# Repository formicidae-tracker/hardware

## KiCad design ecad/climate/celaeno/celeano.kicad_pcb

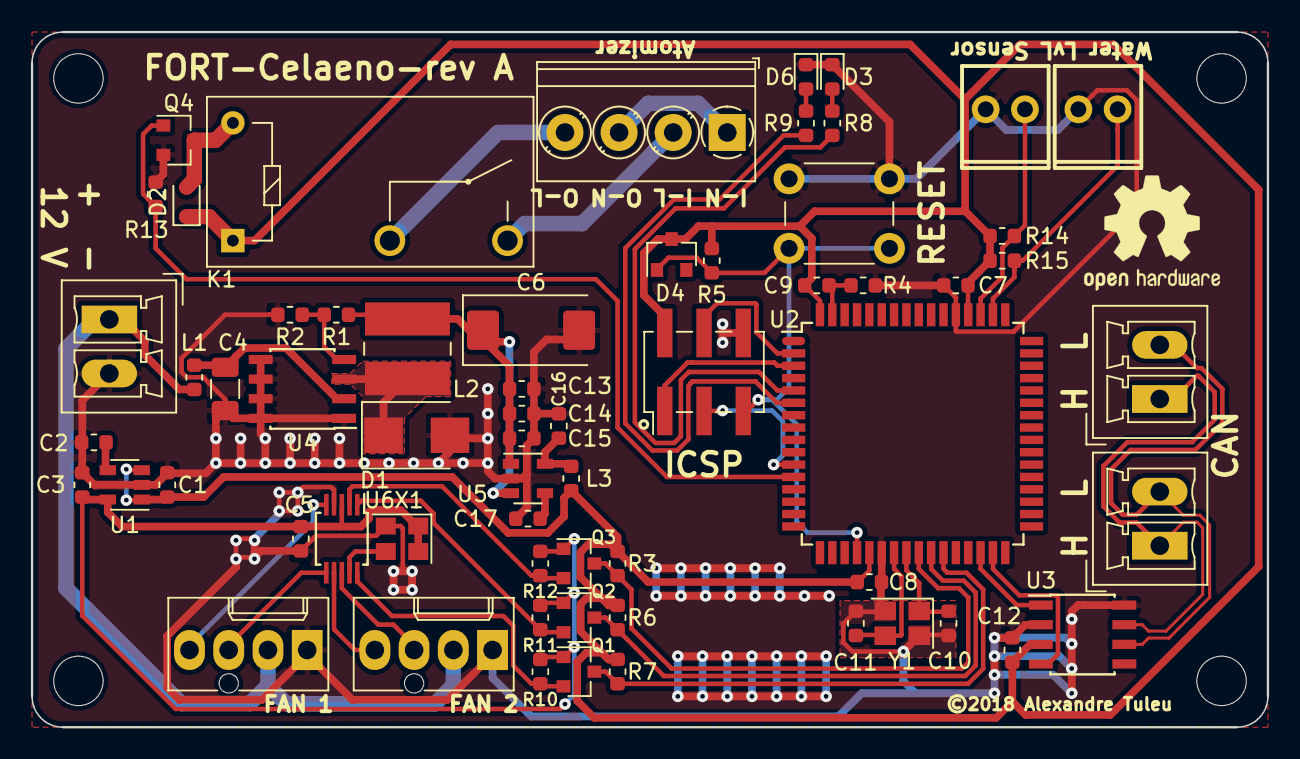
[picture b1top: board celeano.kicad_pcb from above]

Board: 2 copper layers, 80.0 x 45.0 mm, 63 parts (0 on the bottom side), 44 nets.

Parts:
C1, C3: 1uF; C_0603_1608Metric
C2: 10nF; C_0603_1608Metric
C4: 22uF, 35V; C_1206_3216Metric
C5: 100nF; C_0603_1608Metric
C6: 470u, 6.3V; CP_EIA-7343-31_Kemet-D
C7, C8, C9, C12, C14: 100n; C_0603_1608Metric
C10, C11: 18pF; C_0603_1608Metric
C13: 4u7, 6.3V; C_0603_1608Metric
C15, C16: 1u; C_0603_1608Metric
C17: 10n; C_0603_1608Metric
D1: B260, 60V, 2A; D_SMB
D2: 1N4148WS; D_SOD-323F
D3: GREEN; LED_0603_1608Metric
D4: BAT54; D_SOT-23_ANK
D6: YELLOW; LED_0603_1608Metric
J1, J2, J3: MCV 1,5/ 2-G-3,5; PhoenixContact_MCV_1,5_2-G-3.5_1x02_P3.50mm_Vertical
J4: M20-8760342; PinHeader_2x03_P2.54mm_Vertical_SMD
J5, J6: 47053-1000; Molex_KK-47053-04_04x2.54mm_Straight
J7: PT 1,5/4-3,5-H; TerminalBlock_Phoenix_PT-1,5-4-3.5-H_1x04_P3.50mm_Horizontal
J8, J9: 640454-2
K1: G5Q-1A4-EU DC5; Relay_SPST_Omron-G5Q-1A
L1, L3: 500mA Fuse; R_0603_1608Metric
L2: 68uH, 560mA; L_Wuerth_WE-PD2-Typ-MS
Q1, Q2, Q3, Q4: BSS138; SOT-23
R1: 15k; R_0603_1608Metric
R2: 4k32; R_0603_1608Metric
R3, R6, R7, R10, R11, R12: 10k; R_0603_1608Metric
R4: 0R; R_0603_1608Metric
R5, R14, R15: 100k; R_0603_1608Metric
R8, R9: 1k; R_0603_1608Metric
R13: 47k5; R_0603_1608Metric
SW1: 1825910-6; SW_PUSH_6mm
U1: LP3985IM5-3.3/NOPB; SOT-23-5
U2: AT90CAN128-16AU; TQFP-64_14x14mm_P0.8mm
U3: MCP2561-E/SN; SOIC-8_3.9x4.9mm_P1.27mm
U4: MIC4680YM; SOIC-8_3.9x4.9mm_P1.27mm
U5: LP3985IM5-5.0_NOPB; SOT-23-5
U6: EMC2302-1-AIZL-TR; MSOP-10_3x3mm_P0.5mm
X1: 32.768kHz; Oscillator_SMD_Abracon_ASE-4Pin_3.2x2.5mm
Y1: 16MHz; Crystal_SMD_SeikoEpson_FA238-4Pin_3.2x2.5mm

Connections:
+3V3: C3.1, C5.1, Q1.1, Q2.1, Q3.1, R10.1, R11.1, R12.1, U1.5, U6.3, X1.1, X1.4
+5V: C1.1, C7.1, C8.1, C9.1, C12.1, D2.1, D4.1, J4.2, K1.1, L3.1, R3.1, R5.1, R6.1, R7.1, R14.1, R15.1, U1.1, U1.3, U2.21, U2.52, U2.64, U3.3
+12V: J3.1, J5.2, J6.2, L1.2
/3v3 LDO/BYPASS: C2.1, U1.4
/5V Buck Converter/5V5_UNPROTECTED: C6.1, C13.1, C14.1, C15.1, L2.2, R1.1, U5.1, U5.3
/5V Buck Converter/5V_UNPROTECTED: C16.1, L3.2, U5.5
/5V Buck Converter/FB: R1.2, R2.1, U4.4
/5V Buck Converter/SW: D1.1, L2.1, U4.3
/5V Buck Converter/VIN_PROTECTED: C4.1, L1.1, U4.2
/CAN Transceiver/CAN+: J1.1, J2.1, U3.7
/CAN Transceiver/CAN-: J1.2, J2.2, U3.6
/Fan PWM Controller 1/32K768_CLK: U6.9, X1.3
/Fan PWM Controller 1/PWM1: J5.4, U6.5
/Fan PWM Controller 1/PWM2: J6.4, U6.7
/Fan PWM Controller 1/SCL: Q3.2, R12.2, U6.2
/Fan PWM Controller 1/SDA: Q2.2, R11.2, U6.1
/Fan PWM Controller 1/TACH1: J5.3, U6.6
/Fan PWM Controller 1/TACH2: J6.3, U6.8
/Fan PWM Controller 1/~ALERT: Q1.2, R10.2, U6.10
/I2C Level Shifter/SCL_5V: Q3.3, R3.2, U2.25
/I2C Level Shifter/SDA_5V: Q2.3, R6.2, U2.26
/Relay/A: J7.2, K1.3
/Relay/B: J7.4, K1.2
/Relay/CMD: Q4.1, R13.2, U2.12
/UC/CAN_RX: U2.31, U3.4
/UC/CAN_TX: U2.30, U3.1
/UC/ICSP_MISO: J4.1, U2.3
/UC/ICSP_MOSI: J4.4, U2.2
/UC/ICSP_SCK: J4.3, U2.11
/UC/LED_GREEN: R8.1, U2.5
/UC/LED_YELLOW: R9.1, U2.6
/UC/LVL_0: J8.1, R14.2, U2.51
/UC/LVL_1: J9.1, R15.2, U2.50
/UC/XTAL+: C10.2, U2.24, Y1.1
/UC/XTAL-: C11.2, U2.23, Y1.3
/UC/~FAN_ALERT: Q1.3, R7.2, U2.27
/UC/~ICSP_RESET: D4.2, J4.5, R5.2, SW1.2, U2.20
GND: C1.2, C2.2, C3.2, C4.2, C5.2, C6.2, C7.2, C8.2, C10.1, C11.1, C12.2, C13.2, C14.2, C15.2, C16.2, C17.2, D1.2, D3.1, D6.1, J3.2, J4.6, J5.1, J6.1, J8.2, J9.2, Q4.2, R2.2, R4.2, R13.1, SW1.1, U1.2, U2.22, U2.53, U3.2, U3.8, U4.1, U4.5, U4.6, U4.7, U4.8, U5.2, U6.4, X1.2, Y1.2, Y1.4
GNDA: C9.2, R4.1, U2.63
unnamed: C17.1, U5.4
unnamed: D2.2, K1.5, Q4.3
unnamed: D3.2, R8.2
unnamed: D6.2, R9.2
unnamed: J7.1, J7.3

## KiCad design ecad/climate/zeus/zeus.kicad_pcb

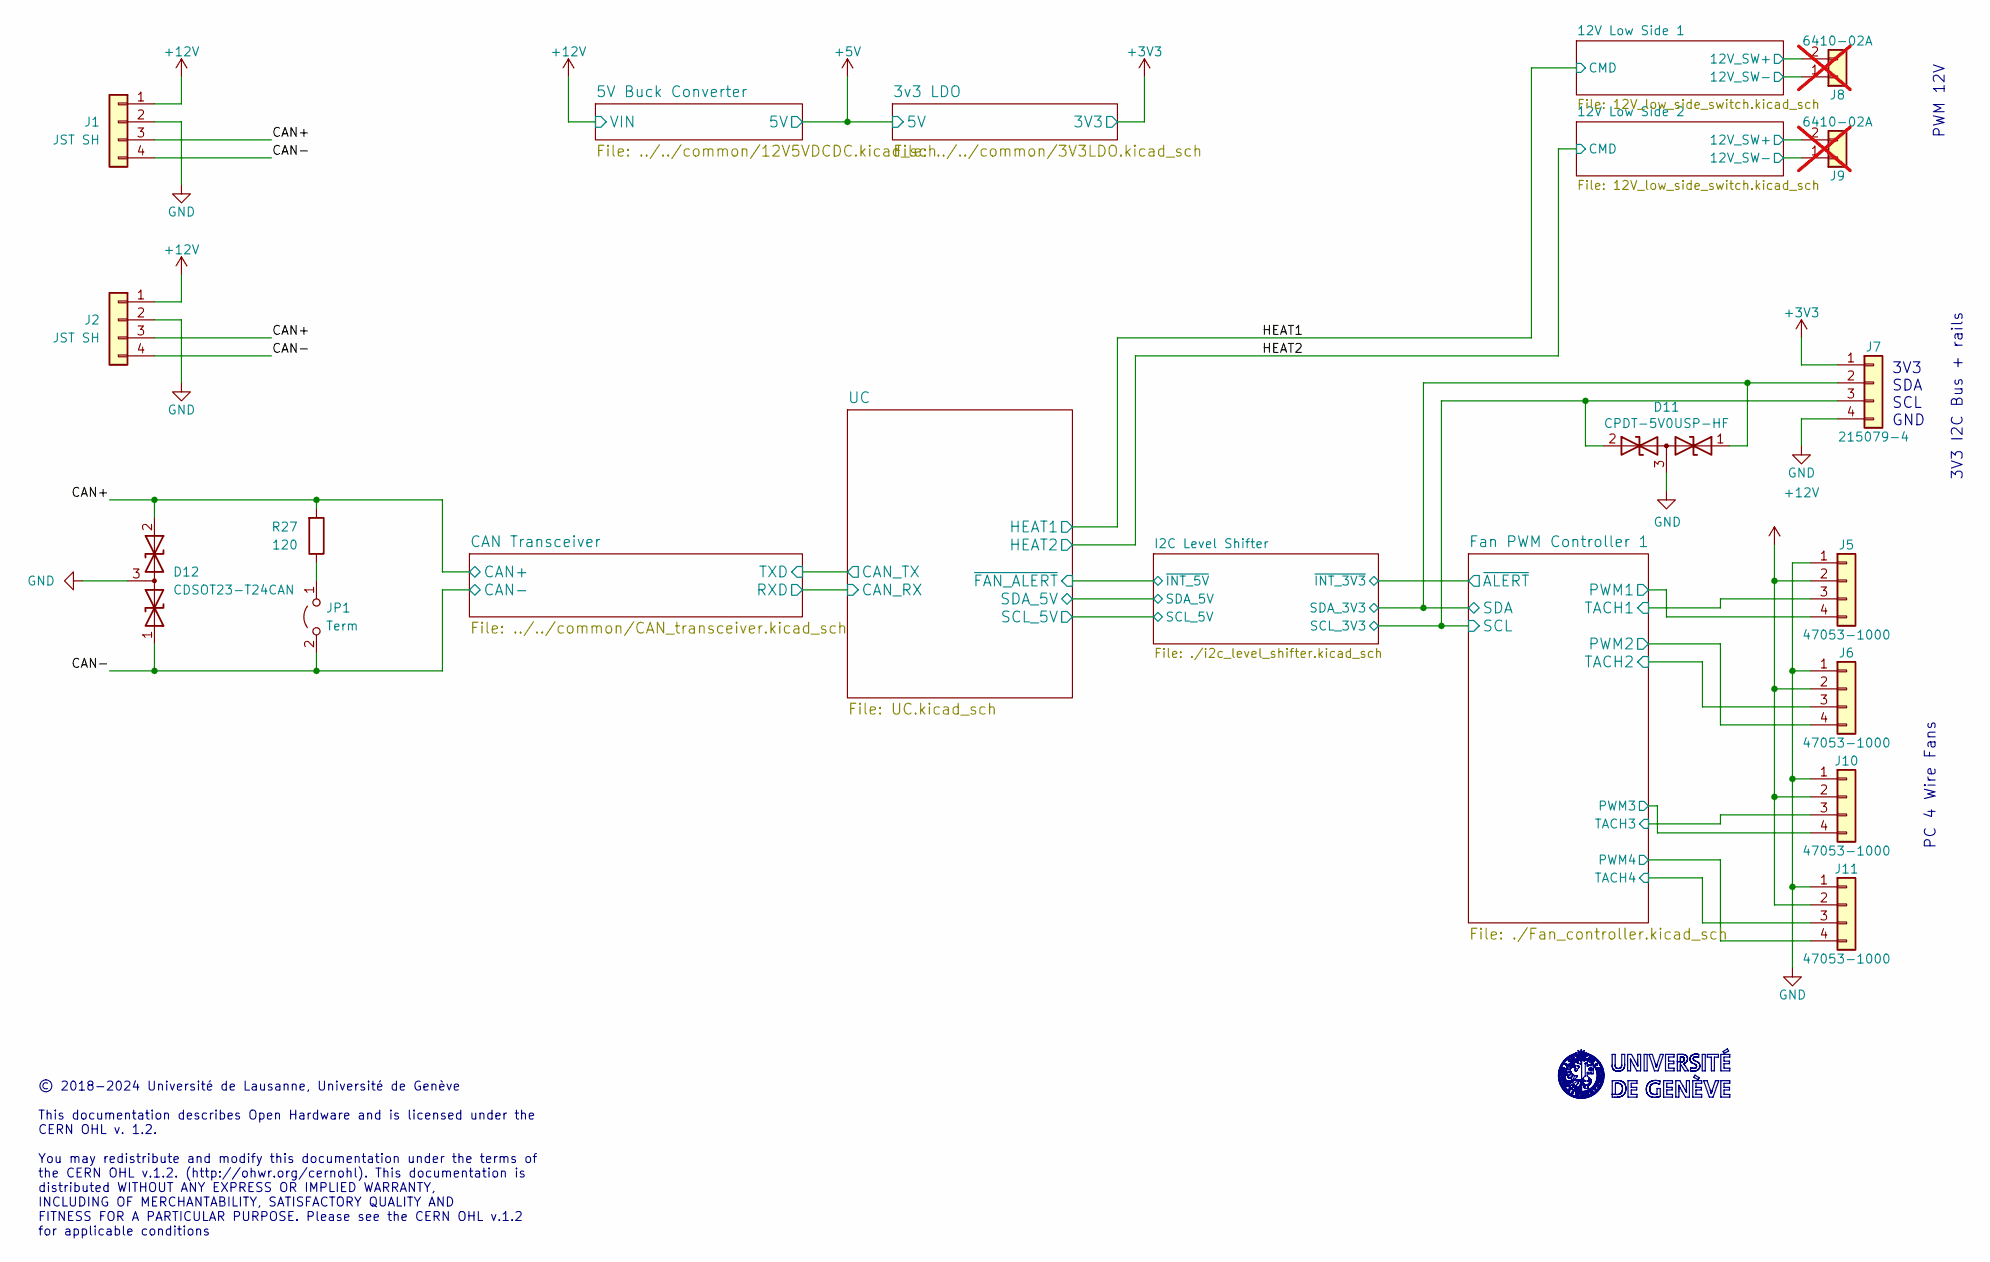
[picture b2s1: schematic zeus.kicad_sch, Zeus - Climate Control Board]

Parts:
D11: CPDT-5V0USP-HF; SOT-23; MPN CPDT-5V0USP-HF
D12: CDSOT23-T24CAN; SOT-23; MPN CDSOT23-T24CAN
J1, J2: JST SH; JST_PH_B4B-PH-SM4-TB_1x04-1MP_P2.00mm_Vertical; MPN B4B-PH-SM4
J5, J6, J10, J11: 47053-1000; Molex_KK-47053-04_04x2.54mm_Straight; MPN 47053-1000
J7: 215079-4; Micro-Match_4_TH; MPN 215079-4
J8, J9: 6410-02A; Molex_KK-254_AE-6410-02A_1x02_P2.54mm_Vertical; MPN 6410-02A; not fitted
JP1: Term; PinHeader_1x02_P2.54mm_Vertical; MPN GPHA-1X02
R27: 120; R_0603_1608Metric; MPN GPR0603120R

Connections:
+3V3: J7.1; also elsewhere on the board
+12V: J1.1, J2.1, J5.2, J6.2, J8.2, J9.2, J10.2, J11.2; also elsewhere on the board
/12V Low Side 1/SW_RTRN: J8.1; also elsewhere on the board
/12V Low Side 2/SW_RTRN: J9.1; also elsewhere on the board
/CAN+: D12.2 (A2), J1.3, J2.3, R27.2; also elsewhere on the board
/CAN-: D12.1 (A1), J1.4, J2.4, JP1.2 (B); also elsewhere on the board
/Fan PWM Controller 1/PWM1: J5.4; also elsewhere on the board
/Fan PWM Controller 1/PWM2: J6.4; also elsewhere on the board
/Fan PWM Controller 1/PWM3: J10.4; also elsewhere on the board
/Fan PWM Controller 1/PWM4: J11.4; also elsewhere on the board
/Fan PWM Controller 1/SCL: D11.2 (A2), J7.3; also elsewhere on the board
/Fan PWM Controller 1/SDA: D11.1 (A1), J7.2; also elsewhere on the board
/Fan PWM Controller 1/TACH1: J5.3; also elsewhere on the board
/Fan PWM Controller 1/TACH2: J6.3; also elsewhere on the board
/Fan PWM Controller 1/TACH3: J10.3; also elsewhere on the board
/Fan PWM Controller 1/TACH4: J11.3; also elsewhere on the board
GND: D11.3 (common), D12.3 (common), J1.2, J2.2, J5.1, J6.1, J7.4, J10.1, J11.1; also elsewhere on the board
unnamed: JP1.1 (A), R27.1

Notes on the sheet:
3V3 I2C Bus + rails
© 2018-2024 Université de Lausanne, Université de Genève This documentation describes Open Hardware and is licensed under the CERN OHL v. 1.2. You may redistribute and modify this documentation under the terms of the CERN OHL v.1.2. (http://ohwr.org/cernohl). This documentation is distributed WITHO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
3V3 SDA SCL GND
PWM 12V
PC 4 Wire Fans

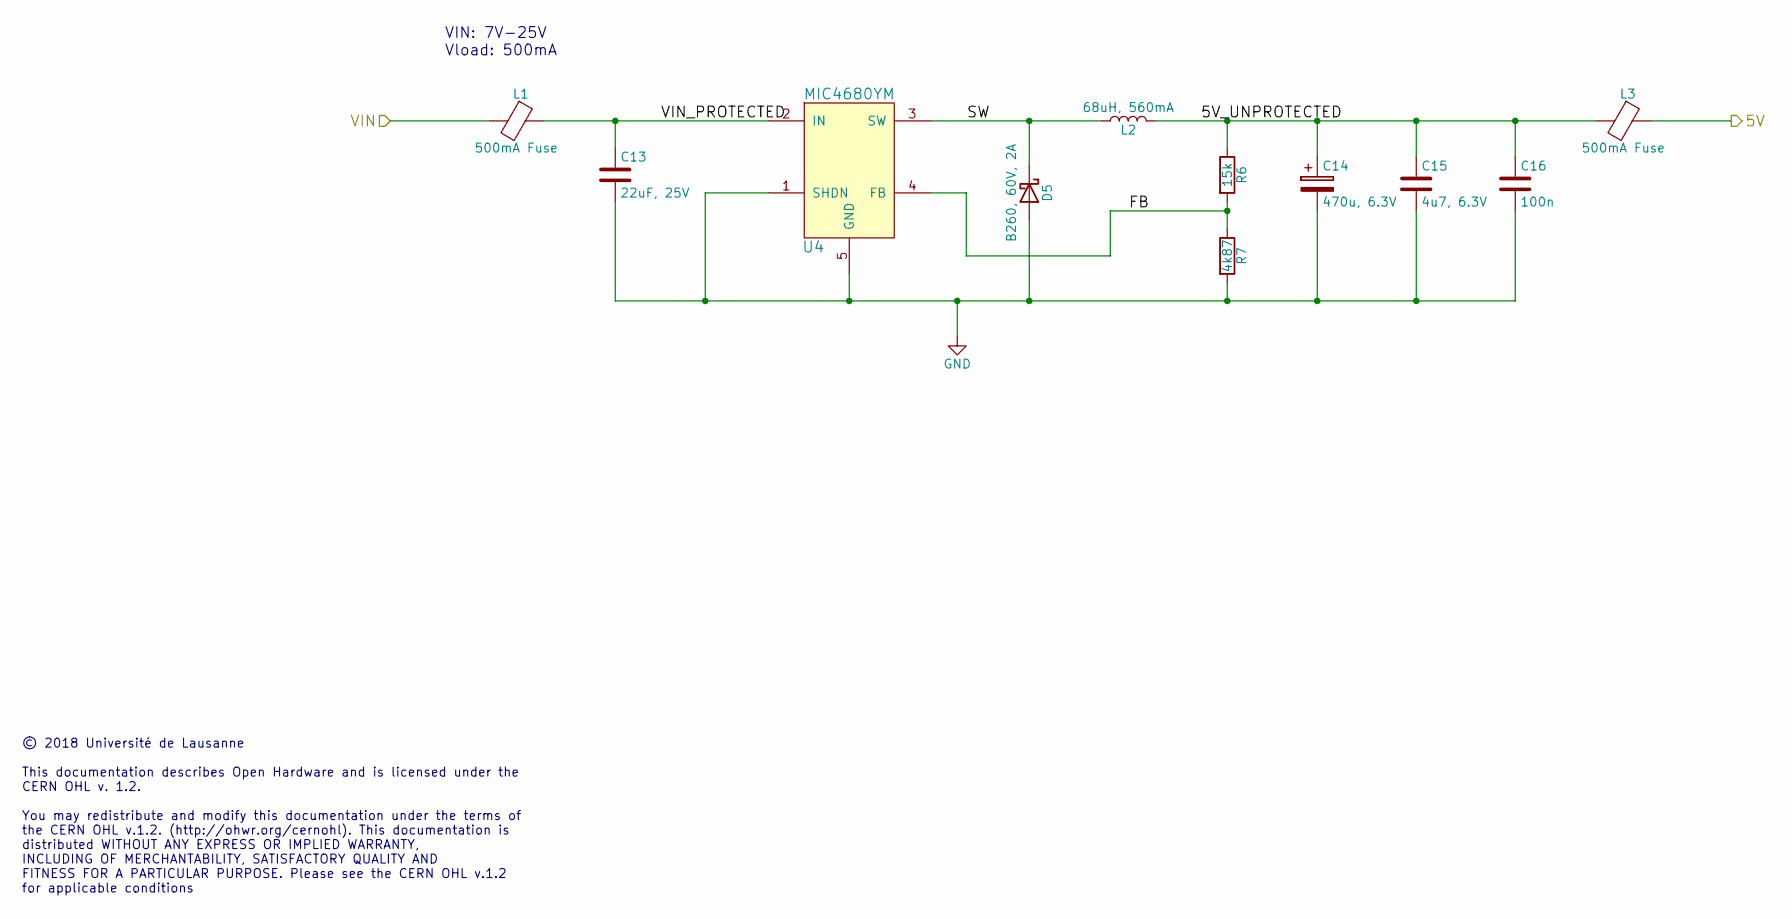
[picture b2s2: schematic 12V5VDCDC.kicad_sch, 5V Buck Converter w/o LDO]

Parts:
C13: 22uF, 25V; C_1206_3216Metric; MPN CL31A226KAHNNNE
C14: 470u, 6.3V; CP_EIA-7343-31_Kemet-D
C15: 4u7, 6.3V; C_0603_1608Metric
C16: 100n; C_0603_1608Metric; MPN GPC0603104
D5: B260, 60V, 2A; D_SMB
L1, L3: 500mA Fuse; R_0603_1608Metric
L2: 68uH, 560mA; L_Wuerth_WE-PD2-Typ-MS
R6: 15k; R_0603_1608Metric
R7: 4k87; R_0603_1608Metric
U4: MIC4680YM; SOIC-8_3.9x4.9mm_P1.27mm

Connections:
+5V: L3.1; also elsewhere on the board
+12V: L1.2; also elsewhere on the board
/5V Buck Converter/5V_UNPROTECTED: C14.1, C15.1, C16.1, L2.2, L3.2, R6.1
/5V Buck Converter/FB: R6.2, R7.1, U4.4 (FB)
/5V Buck Converter/SW: D5.1 (K), L2.1, U4.3 (SW)
/5V Buck Converter/VIN_PROTECTED: C13.1, L1.1, U4.2 (IN)
GND: C13.2, C14.2, C15.2, C16.2, D5.2 (A), R7.2, U4.1 (SHDN), U4.5 (GND), U4.6 (GND), U4.7 (GND), U4.8 (GND); also elsewhere on the board

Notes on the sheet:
© 2018 Université de Lausanne This documentation describes Open Hardware and is licensed under the CERN OHL v. 1.2. You may redistribute and modify this documentation under the terms of the CERN OHL v.1.2. (http://ohwr.org/cernohl). This documentation is distributed WITHOUT ANY EXPRESS OR IMPLIED W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
VIN: 7V-25V Vload: 500mA

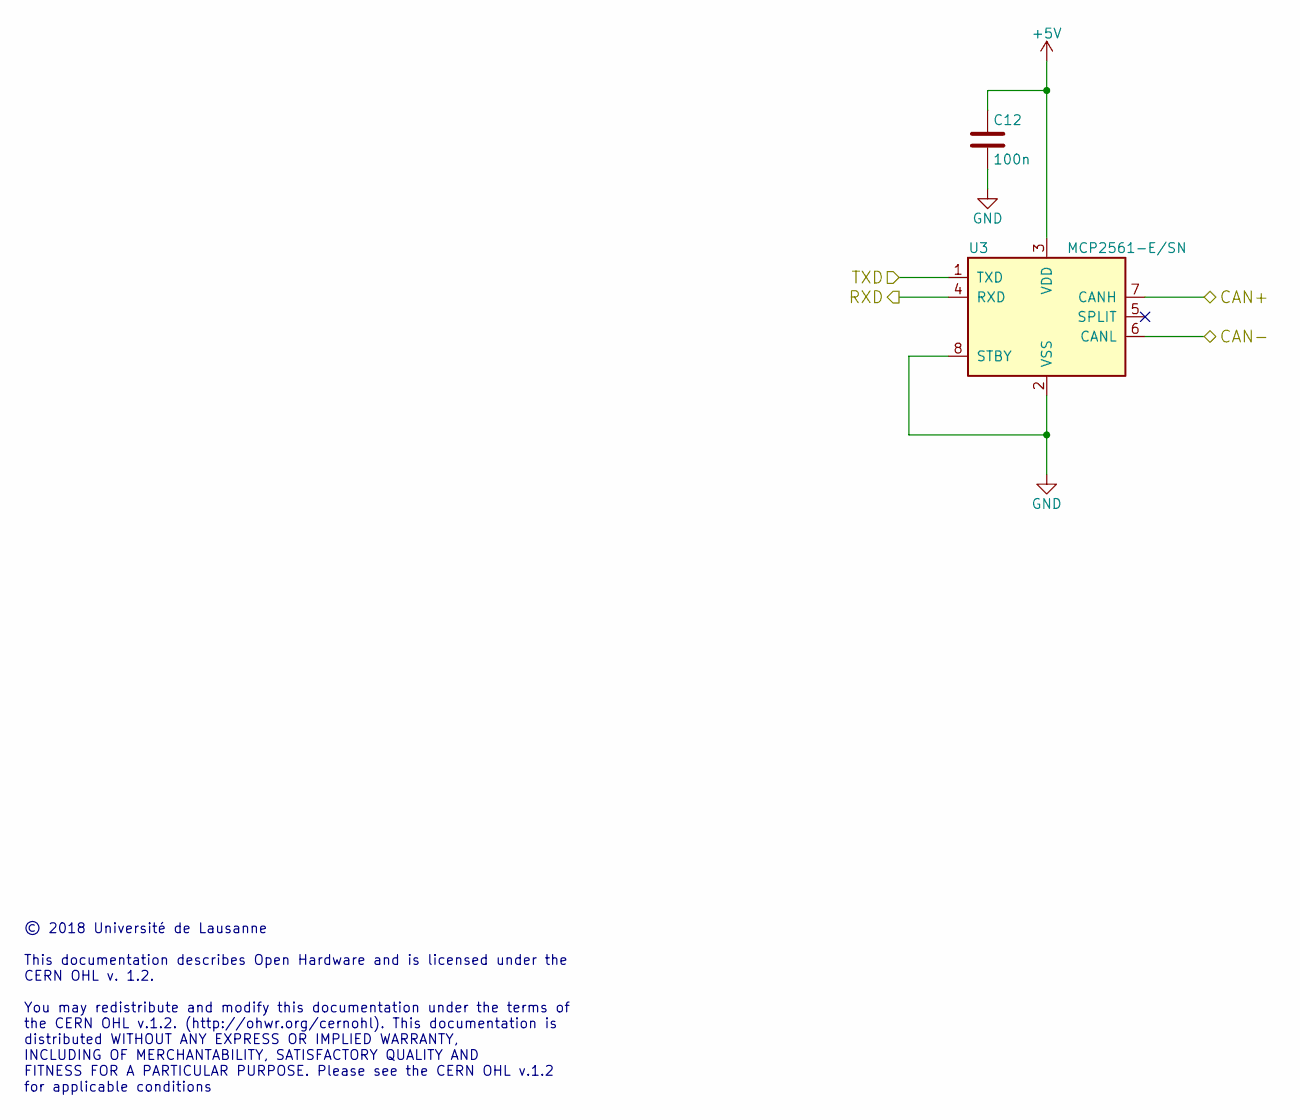
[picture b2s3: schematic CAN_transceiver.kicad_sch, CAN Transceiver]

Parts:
C12: 100n; C_0603_1608Metric; MPN GPC0603104
U3: MCP2561-E/SN; SOIC-8_3.9x4.9mm_P1.27mm

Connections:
+5V: C12.1, U3.3 (VDD); also elsewhere on the board
/CAN Transceiver/RXD: U3.4 (RXD); also elsewhere on the board
/CAN Transceiver/TXD: U3.1 (TXD); also elsewhere on the board
/CAN+: U3.7 (CANH); also elsewhere on the board
/CAN-: U3.6 (CANL); also elsewhere on the board
GND: C12.2, U3.2 (VSS), U3.8 (STBY); also elsewhere on the board

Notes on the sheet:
© 2018 Université de Lausanne This documentation describes Open Hardware and is licensed under the CERN OHL v. 1.2. You may redistribute and modify this documentation under the terms of the CERN OHL v.1.2. (http://ohwr.org/cernohl). This documentation is distributed WITHOUT ANY EXPRESS OR IMPLIED W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

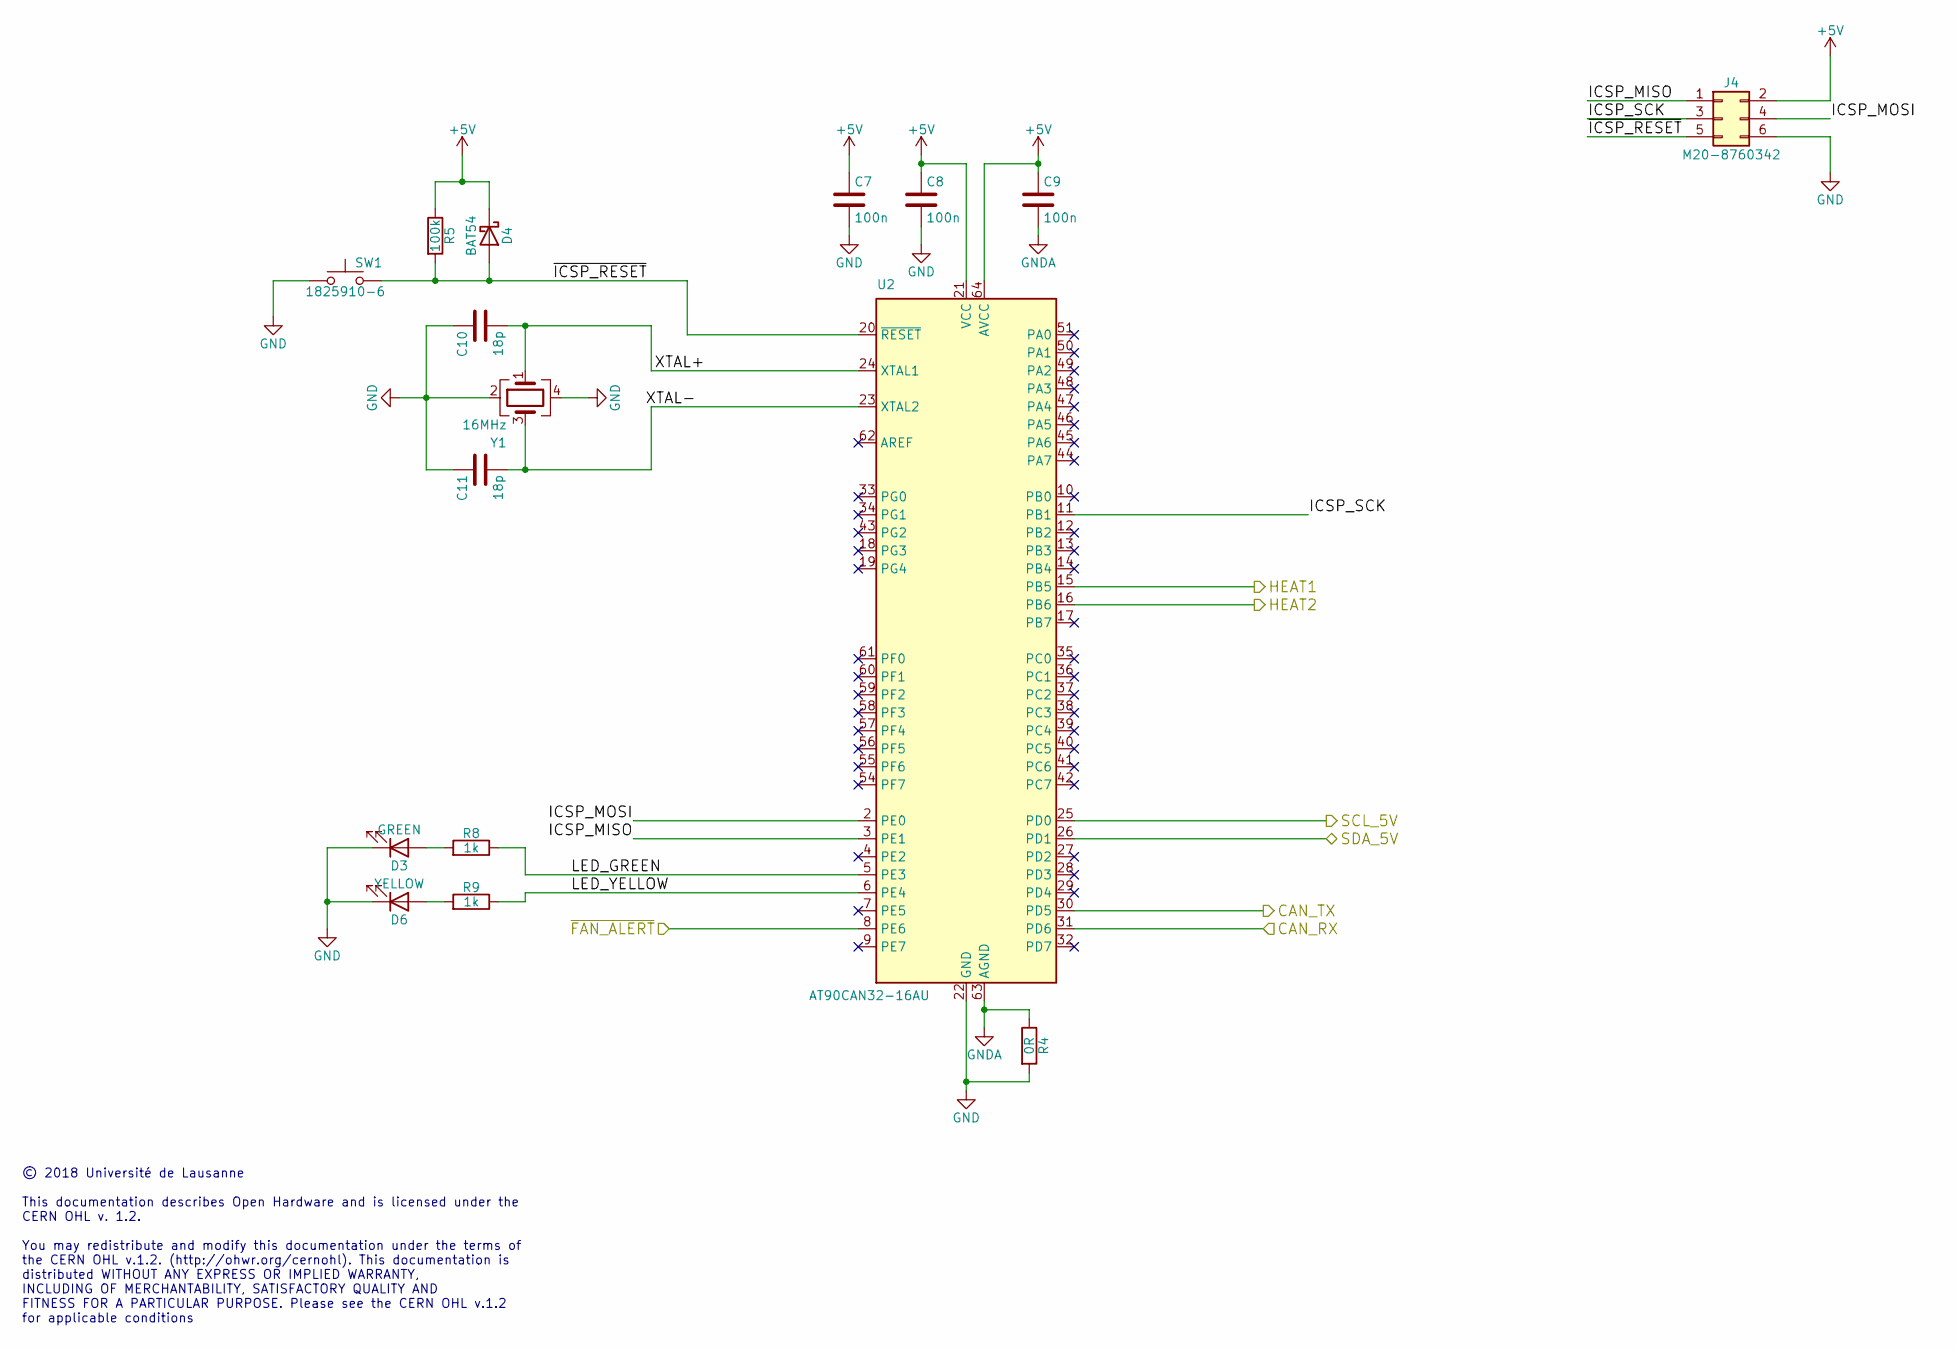
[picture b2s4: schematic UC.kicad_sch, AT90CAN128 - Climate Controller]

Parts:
C7, C8, C9: 100n; C_0603_1608Metric; MPN GPC0603104
C10, C11: 18p; C_0603_1608Metric; MPN GPC0603180
D3: GREEN; LED_0603_1608Metric; MPN 150060VS75000
D4: BAT54; D_SOT-23_ANK; MPN BAT54-7-F
D6: YELLOW; LED_0603_1608Metric; MPN 150060YS75000
J4: M20-8760342; PinHeader_2x03_P2.54mm_Vertical_SMD; MPN M20-8760342
R4: 0R; R_0603_1608Metric; MPN GPR06030R
R5: 100k; R_0603_1608Metric; MPN GPR0603100K
R8, R9: 1k; R_0603_1608Metric; MPN GPR06031K
SW1: 1825910-6; SW_PUSH_6mm; MPN 1825910-6
U2: AT90CAN32-16AU; TQFP-64_14x14mm_P0.8mm; MPN AT90CAN32-16AU
Y1: 16MHz; Crystal_SMD_SeikoEpson_FA238-4Pin_3.2x2.5mm; MPN FA-238 16.0000MB-C3

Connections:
+5V: C7.1, C8.1, C9.1, D4.1 (K), J4.2, R5.1, U2.21 (VCC), U2.52 (VCC), U2.64 (AVCC); also elsewhere on the board
/CAN Transceiver/RXD: U2.31 (PD6); also elsewhere on the board
/CAN Transceiver/TXD: U2.30 (PD5); also elsewhere on the board
/I2C Level Shifter/SCL_5V: U2.25 (PD0); also elsewhere on the board
/I2C Level Shifter/SDA_5V: U2.26 (PD1); also elsewhere on the board
/I2C Level Shifter/~INT_5V: U2.8 (PE6); also elsewhere on the board
/UC/ICSP_MISO: J4.1, U2.3 (PE1)
/UC/ICSP_MOSI: J4.4, U2.2 (PE0)
/UC/ICSP_SCK: J4.3, U2.11 (PB1)
/UC/LED_GREEN: R8.1, U2.5 (PE3)
/UC/LED_YELLOW: R9.1, U2.6 (PE4)
/UC/XTAL+: C10.2, U2.24 (XTAL1), Y1.1
/UC/XTAL-: C11.2, U2.23 (XTAL2), Y1.3
/UC/~ICSP_RESET: D4.2 (A), J4.5, R5.2, SW1.2, U2.20 (~RESET)
GND: C7.2, C8.2, C10.1, C11.1, D3.1 (K), D6.1 (K), J4.6, R4.2, SW1.1, U2.22 (GND), U2.53 (GND), Y1.2, Y1.4; also elsewhere on the board
GNDA: C9.2, R4.1, U2.63 (AGND)
unnamed: D3.2 (A), R8.2
unnamed: D6.2 (A), R9.2

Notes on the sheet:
© 2018 Université de Lausanne This documentation describes Open Hardware and is licensed under the CERN OHL v. 1.2. You may redistribute and modify this documentation under the terms of the CERN OHL v.1.2. (http://ohwr.org/cernohl). This documentation is distributed WITHOUT ANY EXPRESS OR IMPLIED W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

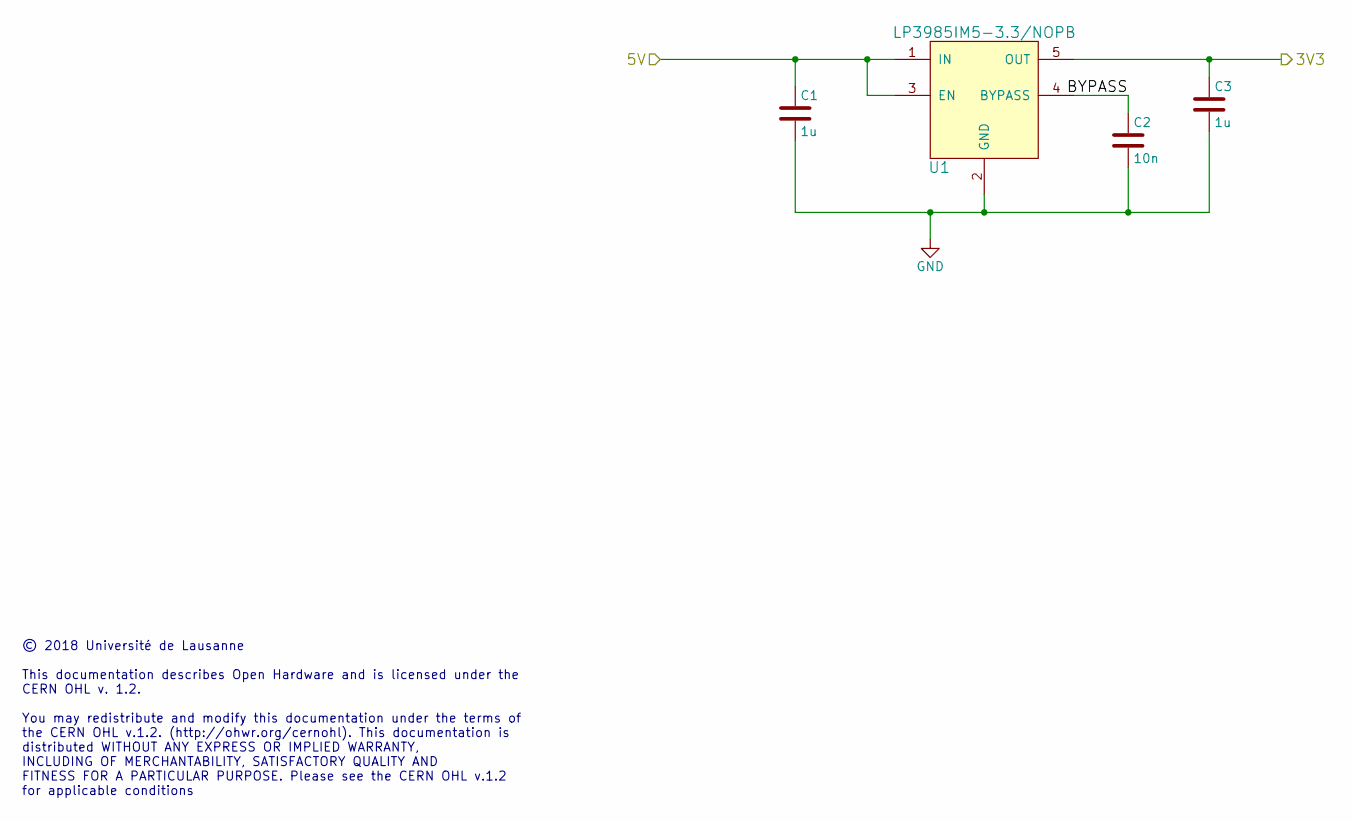
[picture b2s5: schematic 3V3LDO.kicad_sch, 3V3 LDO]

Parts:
C1, C3: 1u; C_0603_1608Metric; MPN GPC0603105
C2: 10n; C_0603_1608Metric; MPN GPC0603103
U1: LP3985IM5-3.3/NOPB; SOT-23-5

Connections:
+3V3: C3.1, U1.5 (OUT); also elsewhere on the board
+5V: C1.1, U1.1 (IN), U1.3 (EN); also elsewhere on the board
/3v3 LDO/BYPASS: C2.1, U1.4 (BYPASS)
GND: C1.2, C2.2, C3.2, U1.2 (GND); also elsewhere on the board

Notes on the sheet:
© 2018 Université de Lausanne This documentation describes Open Hardware and is licensed under the CERN OHL v. 1.2. You may redistribute and modify this documentation under the terms of the CERN OHL v.1.2. (http://ohwr.org/cernohl). This documentation is distributed WITHOUT ANY EXPRESS OR IMPLIED W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

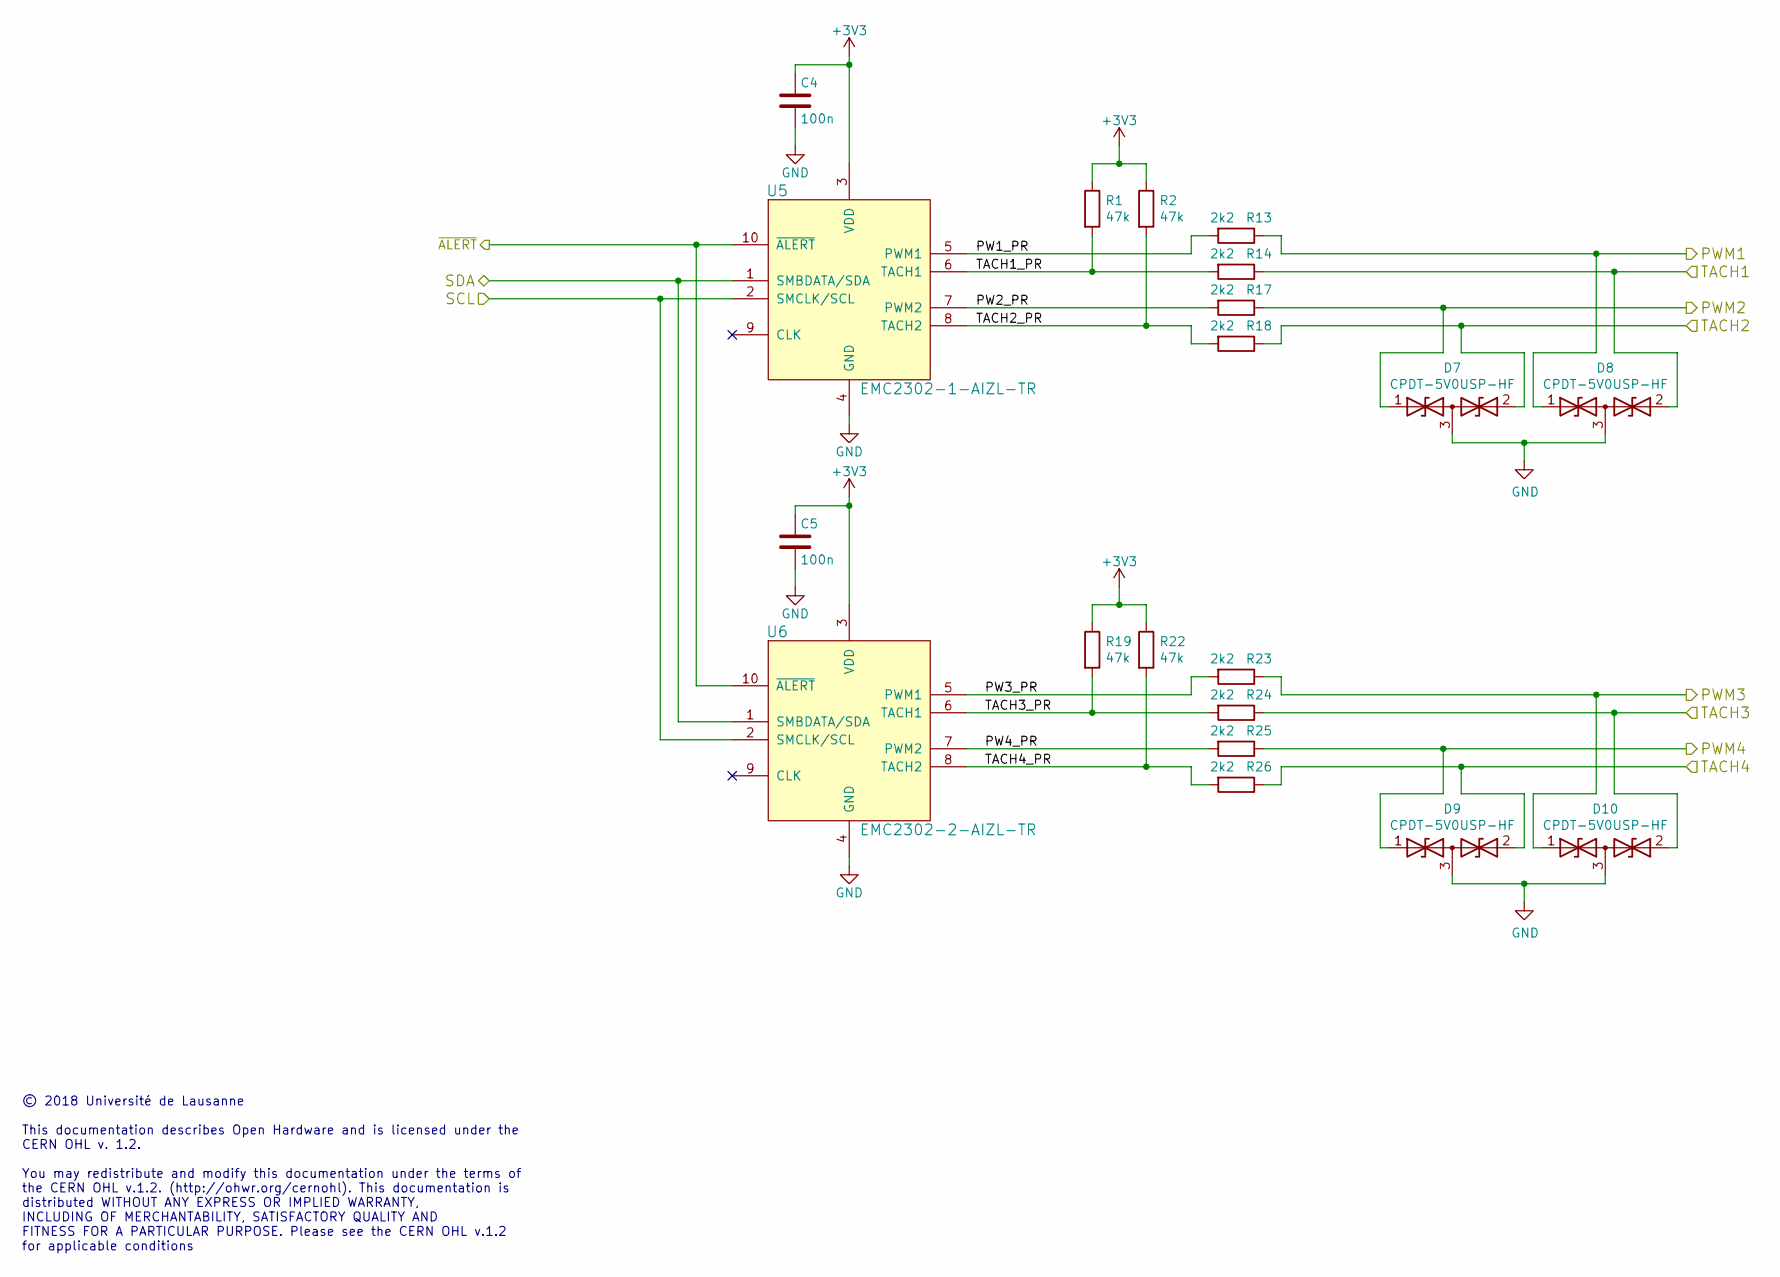
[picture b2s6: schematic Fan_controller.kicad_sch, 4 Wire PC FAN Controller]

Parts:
C4, C5: 100n; C_0603_1608Metric; MPN GPC0603104
D7, D8, D9, D10: CPDT-5V0USP-HF; SOT-23; MPN CPDT-5V0USP-HF
R1, R2, R19, R22: 47k; R_0603_1608Metric; MPN GPR060347K
R13, R14, R17, R18, R23, R24, R25, R26: 2k2; R_0603_1608Metric; MPN GPR06032K2
U5: EMC2302-1-AIZL-TR; MSOP-10_3x3mm_P0.5mm; MPN EMC2302-1-AIZL-TR
U6: EMC2302-2-AIZL-TR; MSOP-10_3x3mm_P0.5mm; MPN EMC2302-2-AIZL-TR

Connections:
+3V3: C4.1, C5.1, R1.1, R2.1, R19.1, R22.1, U5.3 (VDD), U6.3 (VDD); also elsewhere on the board
/Fan PWM Controller 1/PW1_PR: R13.2, U5.5 (PWM1)
/Fan PWM Controller 1/PW2_PR: R17.2, U5.7 (PWM2)
/Fan PWM Controller 1/PW3_PR: R23.2, U6.5 (PWM1)
/Fan PWM Controller 1/PW4_PR: R25.2, U6.7 (PWM2)
/Fan PWM Controller 1/PWM1: D8.1 (A1), R13.1; also elsewhere on the board
/Fan PWM Controller 1/PWM2: D7.1 (A1), R17.1; also elsewhere on the board
/Fan PWM Controller 1/PWM3: D10.1 (A1), R23.1; also elsewhere on the board
/Fan PWM Controller 1/PWM4: D9.1 (A1), R25.1; also elsewhere on the board
/Fan PWM Controller 1/SCL: U5.2 (SMCLK/SCL), U6.2 (SMCLK/SCL); also elsewhere on the board
/Fan PWM Controller 1/SDA: U5.1 (SMBDATA/SDA), U6.1 (SMBDATA/SDA); also elsewhere on the board
/Fan PWM Controller 1/TACH1: D8.2 (A2), R14.1; also elsewhere on the board
/Fan PWM Controller 1/TACH1_PR: R1.2, R14.2, U5.6 (TACH1)
/Fan PWM Controller 1/TACH2: D7.2 (A2), R18.1; also elsewhere on the board
/Fan PWM Controller 1/TACH2_PR: R2.2, R18.2, U5.8 (TACH2)
/Fan PWM Controller 1/TACH3: D10.2 (A2), R24.1; also elsewhere on the board
/Fan PWM Controller 1/TACH3_PR: R19.2, R24.2, U6.6 (TACH1)
/Fan PWM Controller 1/TACH4: D9.2 (A2), R26.1; also elsewhere on the board
/Fan PWM Controller 1/TACH4_PR: R22.2, R26.2, U6.8 (TACH2)
/Fan PWM Controller 1/~ALERT: U5.10 (~ALERT), U6.10 (~ALERT); also elsewhere on the board
GND: C4.2, C5.2, D7.3 (common), D8.3 (common), D9.3 (common), D10.3 (common), U5.4 (GND), U6.4 (GND); also elsewhere on the board

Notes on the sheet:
© 2018 Université de Lausanne This documentation describes Open Hardware and is licensed under the CERN OHL v. 1.2. You may redistribute and modify this documentation under the terms of the CERN OHL v.1.2. (http://ohwr.org/cernohl). This documentation is distributed WITHOUT ANY EXPRESS OR IMPLIED W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

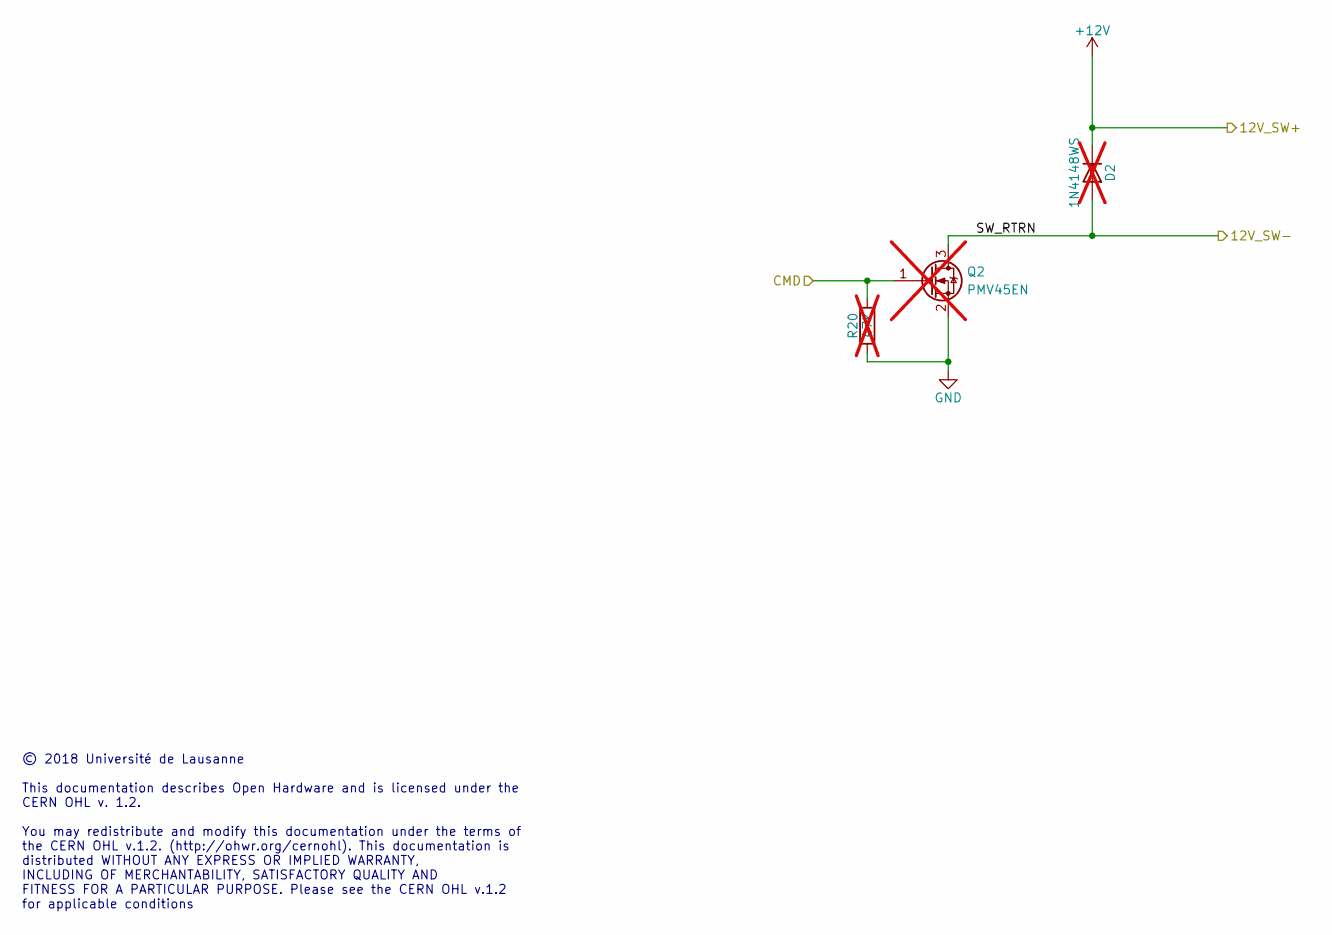
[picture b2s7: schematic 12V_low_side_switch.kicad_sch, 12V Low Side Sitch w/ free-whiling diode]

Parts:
D2: 1N4148WS; D_SOD-323F; MPN 1N4148WS; not fitted
Q2: PMV45EN; SOT-23; MPN PMV45EN2R; not fitted
R20: 47k; R_0603_1608Metric; MPN GPR060347K; not fitted

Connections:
+12V: D2.1 (K); also elsewhere on the board
/12V Low Side 2/SW_RTRN: D2.2 (A), Q2.3 (D); also elsewhere on the board
GND: Q2.2 (S), R20.1; also elsewhere on the board

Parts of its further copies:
D1: 1N4148WS; D_SOD-323F; MPN 1N4148WS; not fitted
Q1: PMV45EN; SOT-23; MPN PMV45EN2R; not fitted
R21: 47k; R_0603_1608Metric; MPN GPR060347K; not fitted

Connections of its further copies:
+12V: D1.1 (K); also elsewhere on the board
/12V Low Side 1/SW_RTRN: D1.2 (A), Q1.3 (D); also elsewhere on the board
GND: Q1.2 (S), R21.1; also elsewhere on the board

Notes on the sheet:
© 2018 Université de Lausanne This documentation describes Open Hardware and is licensed under the CERN OHL v. 1.2. You may redistribute and modify this documentation under the terms of the CERN OHL v.1.2. (http://ohwr.org/cernohl). This documentation is distributed WITHOUT ANY EXPRESS OR IMPLIED W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

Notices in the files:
ecad/climate/celaeno/celeano.kicad_pcb:
©2018 Alexandre Tuleu
ecad/climate/zeus/zeus.kicad_pcb:
© 2024 Université de Genève
